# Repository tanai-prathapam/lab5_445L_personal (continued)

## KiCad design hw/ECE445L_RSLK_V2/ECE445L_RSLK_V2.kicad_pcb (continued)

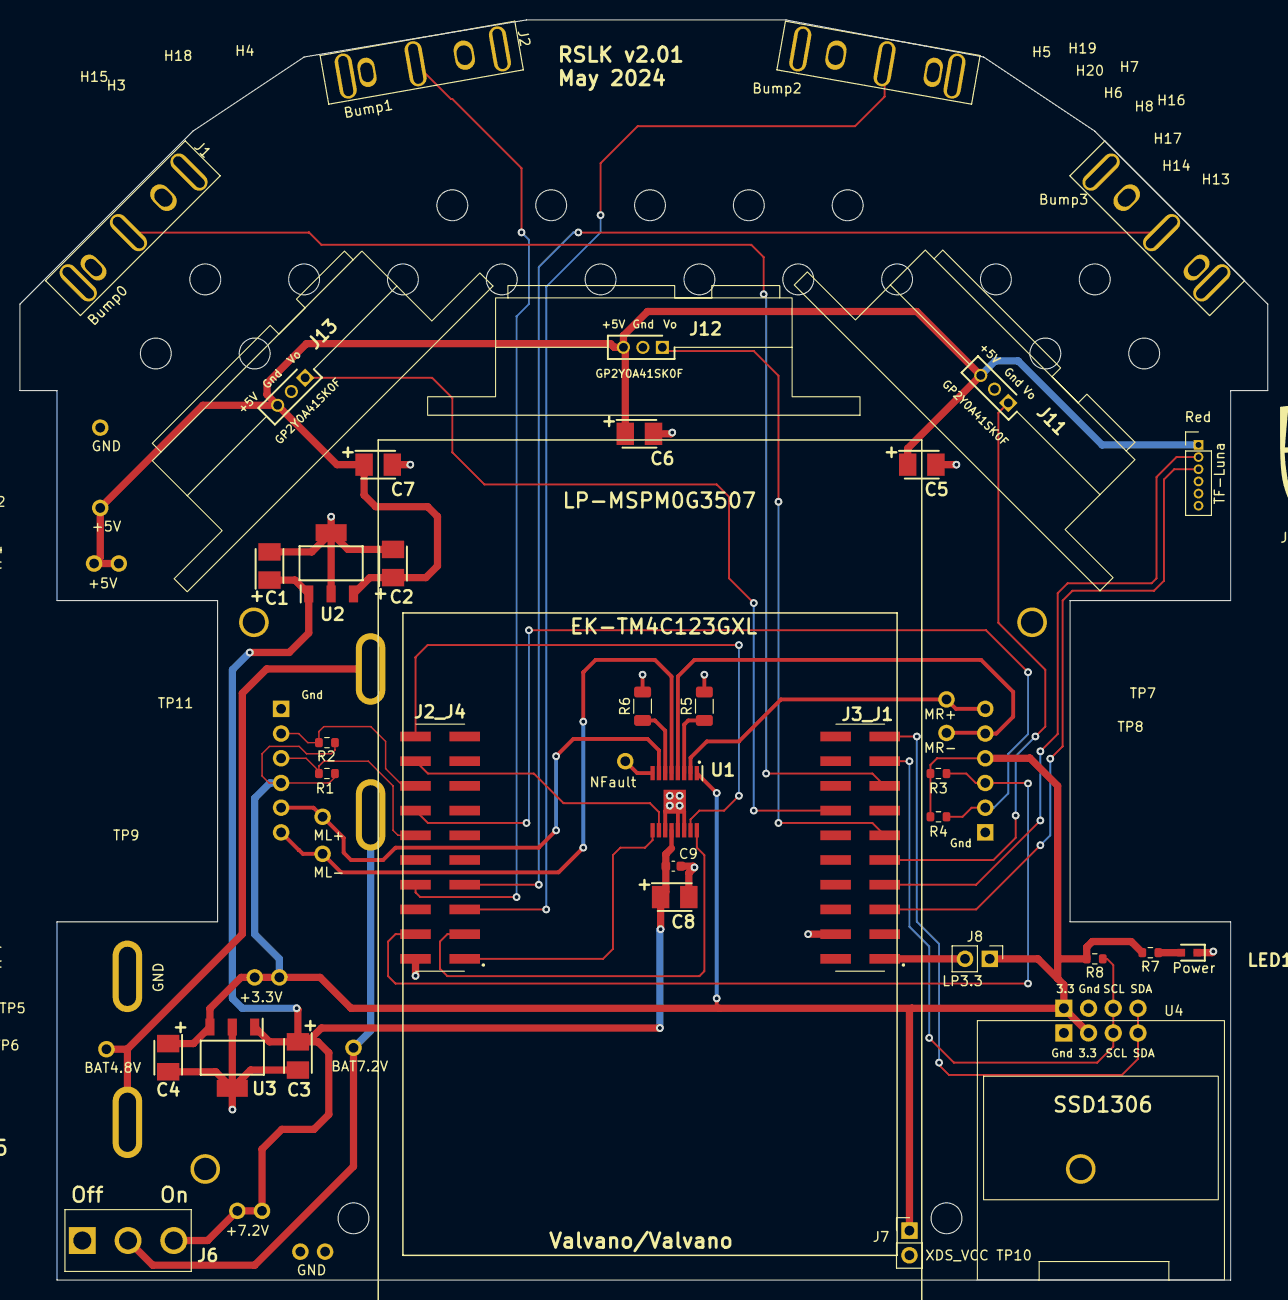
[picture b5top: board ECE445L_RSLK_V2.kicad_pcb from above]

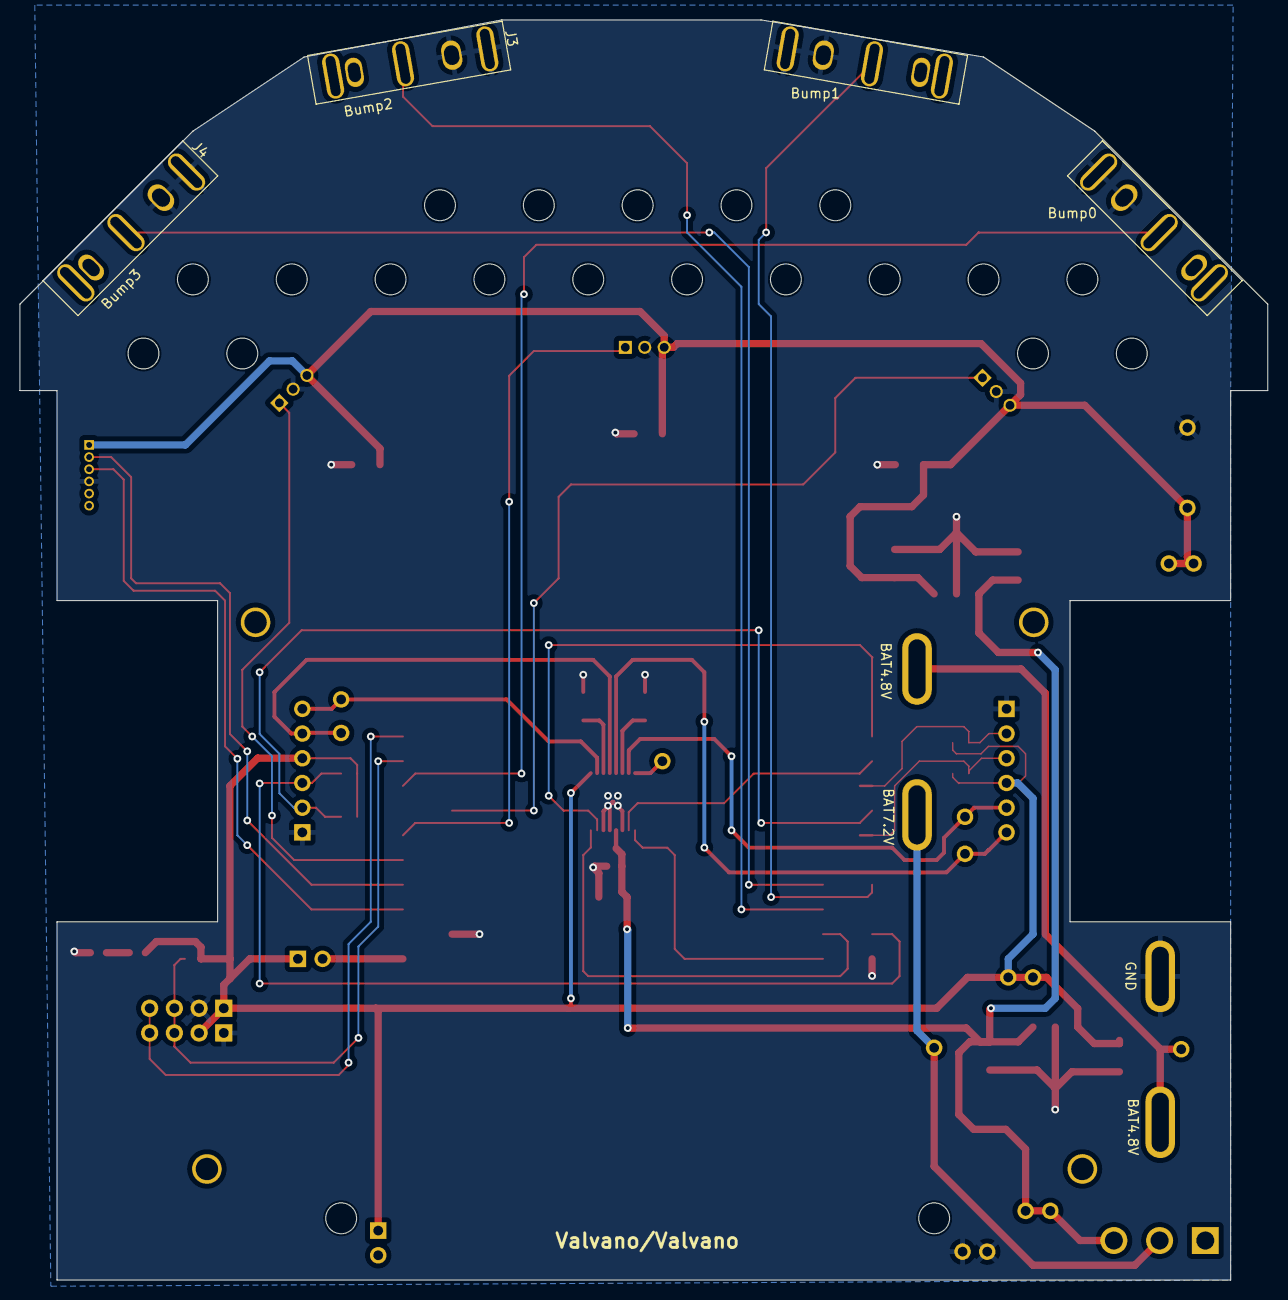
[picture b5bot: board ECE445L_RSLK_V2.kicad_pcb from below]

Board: 2 copper layers, 128.3 x 129.5 mm, 70 parts (2 on the bottom side), 34 nets.

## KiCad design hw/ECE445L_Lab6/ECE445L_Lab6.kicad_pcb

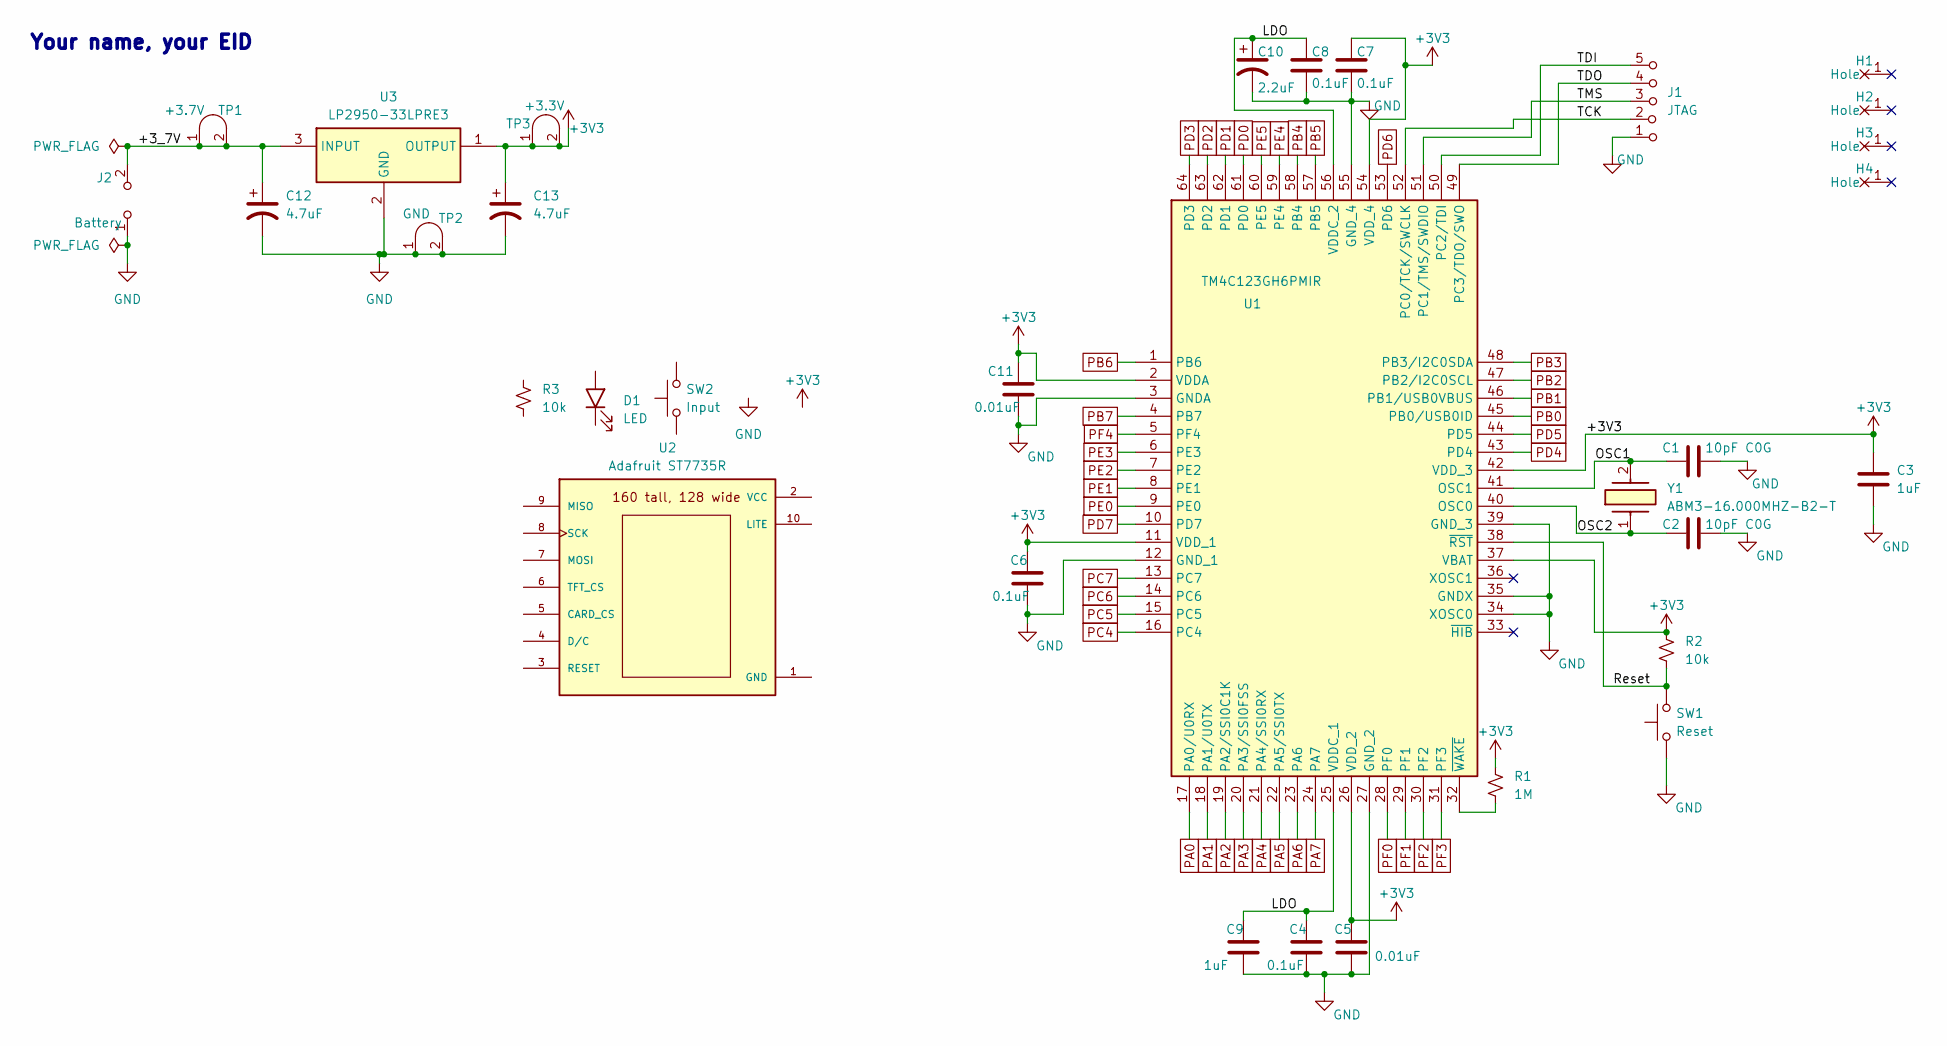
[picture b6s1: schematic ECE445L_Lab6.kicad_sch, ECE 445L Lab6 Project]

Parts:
C1, C2: 10pF C0G; C_Axial_200mil
C3, C9: 1uF; C_Axial_200mil
C4, C6, C7, C8: 0.1uF; C_Axial_200mil
C5, C11: 0.01uF; C_Axial_200mil
C10: 2.2uF; CP_Radial_Tantal200mil
C12, C13: 4.7uF; CP_Radial_Tantal200mil
D1: LED; LED_D5.0mm
H1, H2, H3, H4: MountingHole_4_40
J1: JTAG; PinHeader_1x05_P2.54mm_Vertical
J2: Battery; PinHeader_1x02_P2.54mm_Vertical
R1: 1M; R_Axial_DIN0204_L3.6mm_D1.6mm_P7.62mm_Horizontal
R2, R3: 10k; R_Axial_DIN0204_L3.6mm_D1.6mm_P7.62mm_Horizontal
SW1: Reset; SW_PUSH_6mm
SW2: Input; SW_PUSH_6mm
TP1: +3.7V; Testpoint_1x02_P2.54mm
TP2: GND; Testpoint_1x02_P2.54mm
TP3: +3.3V; Testpoint_1x02_P2.54mm
U1: TM4C123GH6PMIR; QFP50P1200X1200X160-64N; Mouser Part Number 595-TM4C123GH6PMIR
U2: Adafruit ST7735R; adafruit_st7735r2
U3: LP2950-33LPRE3; TO-92_Inline_Wide; Mouser Part Number 595-LP2950-33LPRE3
Y1: ABM3-16.000MHZ-B2-T; ABM3; Mouser Part Number 815-ABM3-16-B2-T

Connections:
+3V3: C3.1, C5.1, C6.1, C7.1, C11.1, C13.1, R1.1, R2.1, TP3.1 (A), TP3.2 (B), U1.2 (VDDA), U1.11 (VDD_1), U1.26 (VDD_2), U1.37 (VBAT), U1.42 (VDD_3), U1.54 (VDD_4), U3.1 (OUTPUT)
/+3_7V: C12.1, J2.2 (B), TP1.1 (A), TP1.2 (B), U3.3 (INPUT)
/LDO: C4.1, C8.1, C9.1, C10.1, U1.25 (VDDC_1), U1.56 (VDDC_2)
/OSC1: C1.1, U1.41 (OSC1), Y1.2
/OSC2: C2.1, U1.40 (OSC0), Y1.1
/Reset: R2.2, SW1.2, U1.38 (~RST)
/TCK: J1.2 (B), U1.52 (PC0/TCK/SWCLK)
/TDI: J1.5 (C), U1.50 (PC2/TDI)
/TDO: J1.4 (C), U1.49 (PC3/TDO/SWO)
/TMS: J1.3 (C), U1.51 (PC1/TMS/SWDIO)
GND: C1.2, C2.2, C3.2, C4.2, C5.2, C6.2, C7.2, C8.2, C9.2, C10.2, C11.2, C12.2, C13.2, J1.1 (A), J2.1 (A), SW1.1, TP2.1 (A), TP2.2 (B), U1.3 (GNDA), U1.12 (GND_1), U1.27 (GND_2), U1.34 (XOSC0), U1.35 (GNDX), U1.39 (GND_3), U1.55 (GND_4), U3.2 (GND)
unnamed: R1.2, U1.32 (~WAKE)
PA0: U1.17 (PA0/U0RX)
PA1: U1.18 (PA1/U0TX)
PA2: U1.19 (PA2/SSI0C1K)
PA3: U1.20 (PA3/SSI0FSS)
PA4: U1.21 (PA4/SSI0RX)
PA5: U1.22 (PA5/SSI0TX)
PA6: U1.23 (PA6)
PA7: U1.24 (PA7)
PB0: U1.45 (PB0/USB0ID)
PB1: U1.46 (PB1/USB0VBUS)
PB2: U1.47 (PB2/I2C0SCL)
PB3: U1.48 (PB3/I2C0SDA)
PB4: U1.58 (PB4)
PB5: U1.57 (PB5)
PB6: U1.1 (PB6)
PB7: U1.4 (PB7)
PC4: U1.16 (PC4)
PC5: U1.15 (PC5)
PC6: U1.14 (PC6)
PC7: U1.13 (PC7)
PD0: U1.61 (PD0)
PD1: U1.62 (PD1)
PD2: U1.63 (PD2)
PD3: U1.64 (PD3)
PD4: U1.43 (PD4)
PD5: U1.44 (PD5)
PD6: U1.53 (PD6)
PD7: U1.10 (PD7)
PE0: U1.9 (PE0)
PE1: U1.8 (PE1)
PE2: U1.7 (PE2)
PE3: U1.6 (PE3)
PE4: U1.59 (PE4)
PE5: U1.60 (PE5)
PF0: U1.28 (PF0)
PF1: U1.29 (PF1)
PF2: U1.30 (PF2)
PF3: U1.31 (PF3)
PF4: U1.5 (PF4)

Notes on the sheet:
Your name, your EID

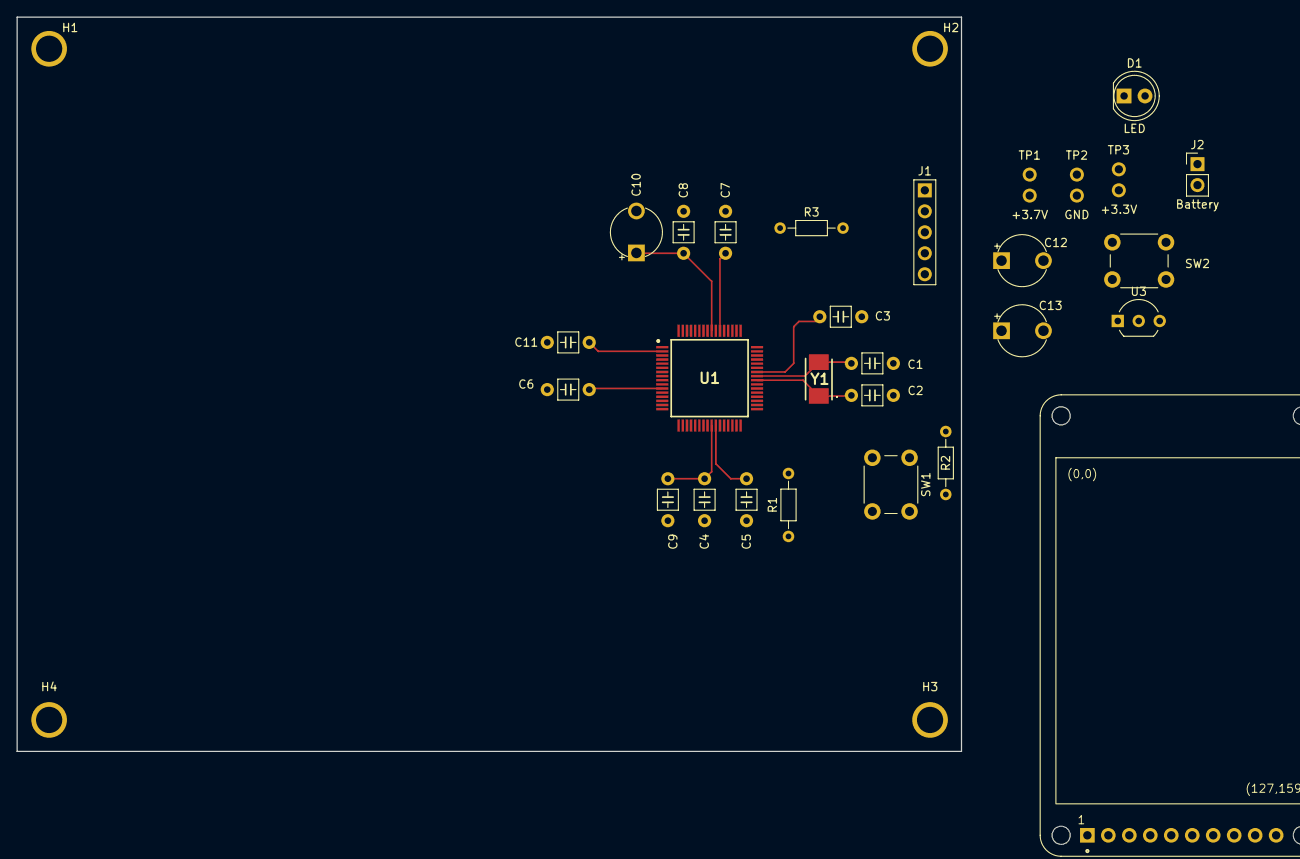
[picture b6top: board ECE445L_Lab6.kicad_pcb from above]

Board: 2 copper layers, 114.4 x 88.9 mm, 32 parts (0 on the bottom side), 12 nets.

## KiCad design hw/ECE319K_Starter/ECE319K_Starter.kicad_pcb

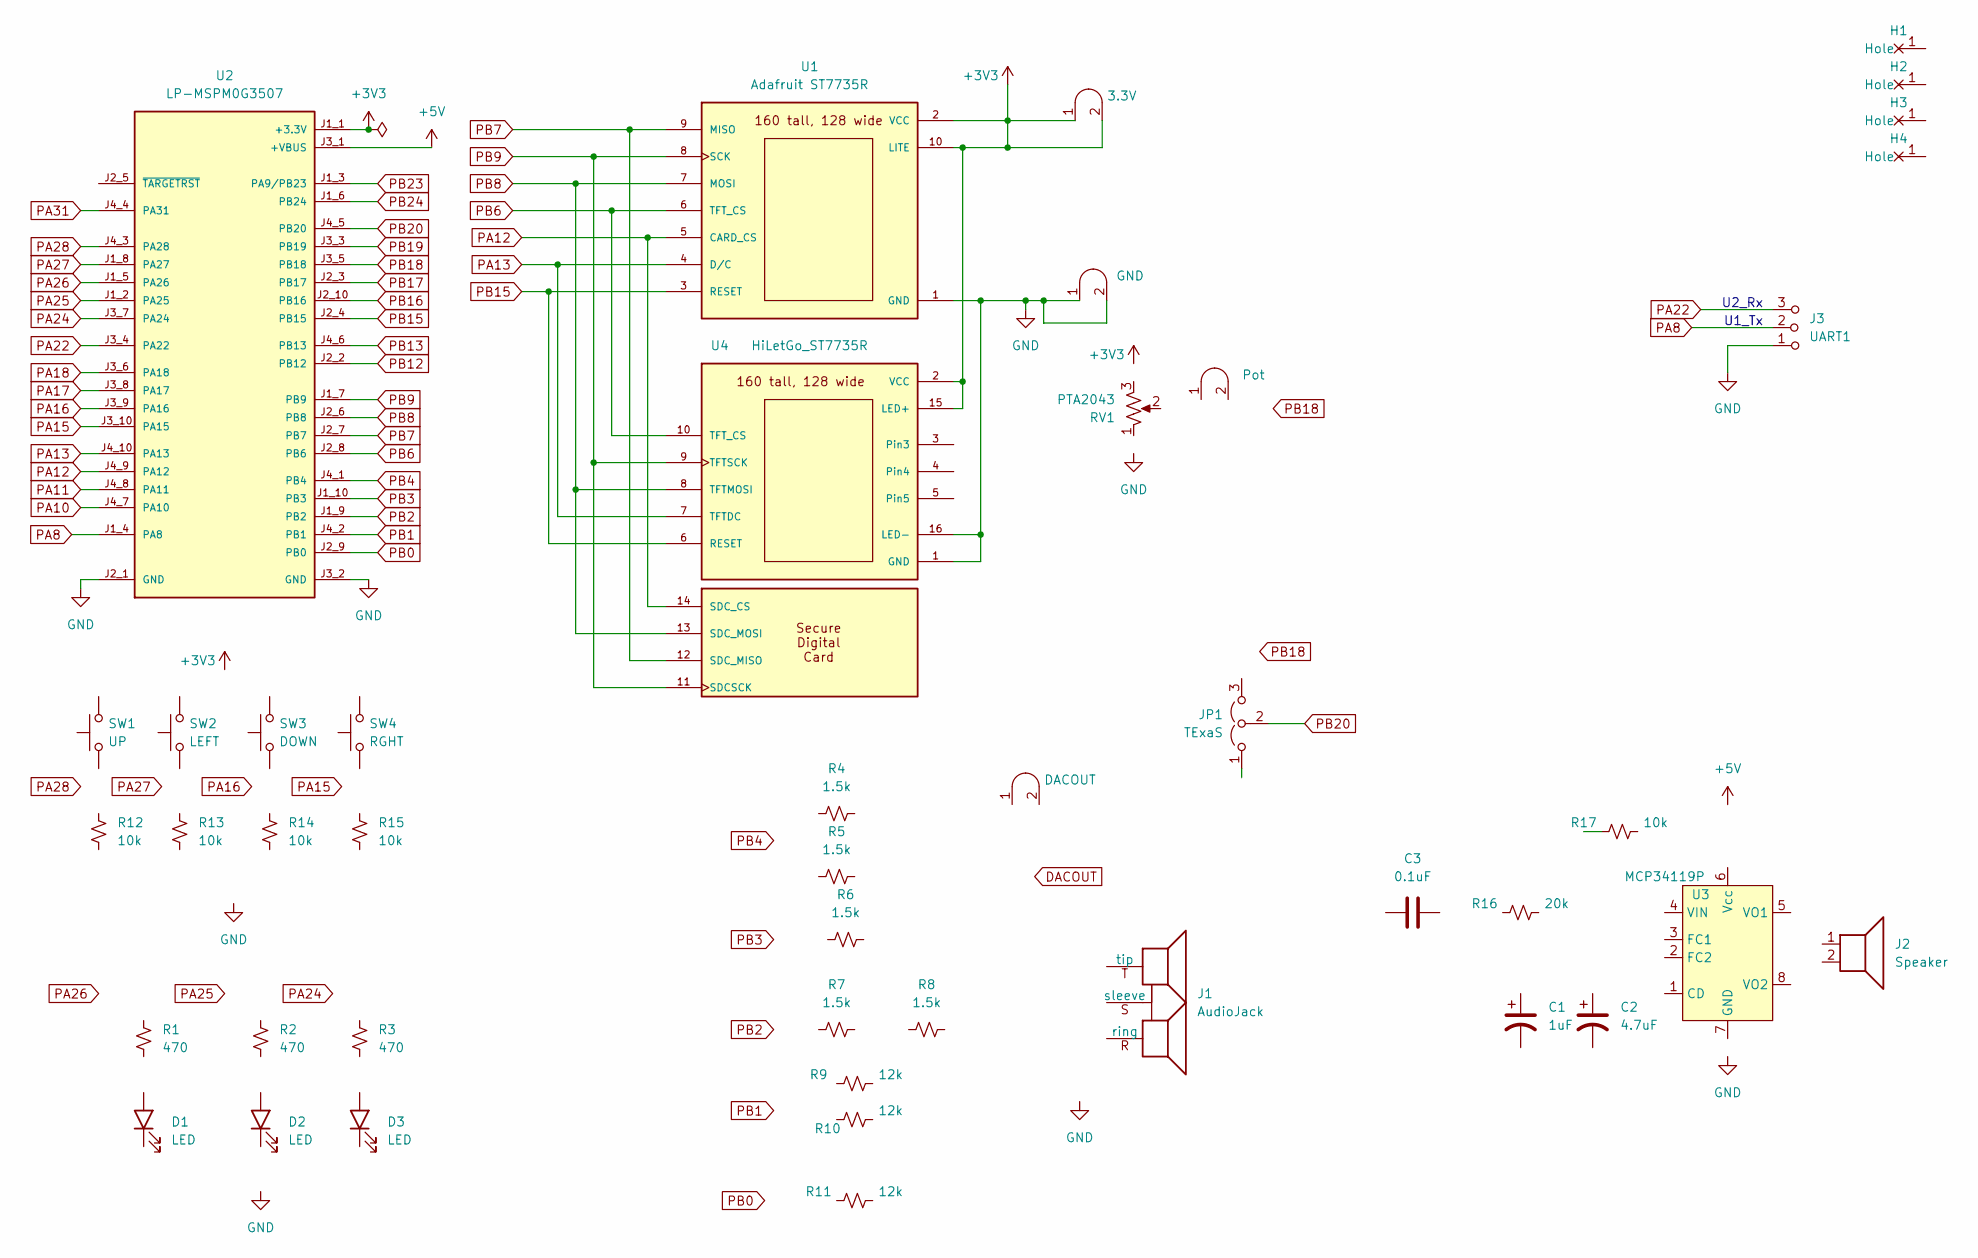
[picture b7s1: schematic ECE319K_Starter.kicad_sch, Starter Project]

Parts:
C1: 1uF; CP_Radial_Tantal200mil
C2: 4.7uF; CP_Radial_Tantal200mil
C3: 0.1uF; C_Axial_200mil
D1, D2, D3: LED; LED_D5.0mm
H1, H2, H3, H4: MountingHole_4_40
J1: AudioJack; Jack_3.5mm_CUI_SJ1-3523N_Horizontal
J2: Speaker; PinHeader_1x02_P2.54mm_Vertical
J3: UART1; PinHeader_1x03_P2.54mm_Vertical
J4: Pot; Testpoint_1x02_P2.54mm
J6: GND; Testpoint_1x02_P2.54mm
J7: DACOUT; Testpoint_1x02_P2.54mm
JP1: TExaS; PinHeader_1x03_P2.54mm_Vertical
R1, R2, R3: 470; R_Axial_DIN0204_L3.6mm_D1.6mm_P7.62mm_Horizontal
R4, R5, R6, R7, R8: 1.5k; R_Axial_DIN0204_L3.6mm_D1.6mm_P7.62mm_Horizontal
R9, R10, R11: 12k; R_Axial_DIN0204_L3.6mm_D1.6mm_P7.62mm_Horizontal
R12, R13, R14, R15, R17: 10k; R_Axial_DIN0204_L3.6mm_D1.6mm_P7.62mm_Horizontal
R16: 20k; R_Axial_DIN0204_L3.6mm_D1.6mm_P7.62mm_Horizontal
RV1: PTA2043; PTA2043pot
SW1: UP; SW_PUSH_6mm
SW2: LEFT; SW_PUSH_6mm
SW3: DOWN; SW_PUSH_6mm
SW4: RGHT; SW_PUSH_6mm
TP1: 3.3V; Testpoint_1x02_P2.54mm
U1: Adafruit ST7735R; adafruit_st7735r2
U2: LP-MSPM0G3507; ti_LP_MSPM0G3507
U3: MCP34119P; DIP-8_W7.62mm_LongPads
U4: HiLetGo_ST7735R; hiletgo_st7735r

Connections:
+3V3: TP1.1 (A), TP1.2 (B), U1.2 (VCC), U1.10 (LITE), U2.J1_1 (+3.3V), U4.2 (VCC), U4.15 (LED+)
+5V: U2.J3_1 (+VBUS)
GND: J3.1 (A), J6.1 (A), J6.2 (B), U1.1 (GND), U2.J2_1 (GND), U2.J3_2 (GND), U4.1 (GND), U4.16 (LED-)
PA8: J3.2 (B), U2.J1_4 (PA8)
PA10: U2.J4_7 (PA10)
PA11: U2.J4_8 (PA11)
PA12: U1.5 (CARD_CS), U2.J4_9 (PA12), U4.14 (SDC_CS)
PA13: U1.4 (D/C), U2.J4_10 (PA13), U4.7 (TFTDC)
PA15: U2.J3_10 (PA15)
PA16: U2.J3_9 (PA16)
PA17: U2.J3_8 (PA17)
PA18: U2.J3_6 (PA18)
PA22: J3.3 (C), U2.J3_4 (PA22)
PA24: U2.J3_7 (PA24)
PA25: U2.J1_2 (PA25)
PA26: U2.J1_5 (PA26)
PA27: U2.J1_8 (PA27)
PA28: U2.J4_3 (PA28)
PA31: U2.J4_4 (PA31)
PB0: U2.J2_9 (PB0)
PB1: U2.J4_2 (PB1)
PB2: U2.J1_9 (PB2)
PB3: U2.J1_10 (PB3)
PB4: U2.J4_1 (PB4)
PB6: U1.6 (TFT_CS), U2.J2_8 (PB6), U4.10 (TFT_CS)
PB7: U1.9 (MISO), U2.J2_7 (PB7), U4.12 (SDC_MISO)
PB8: U1.7 (MOSI), U2.J2_6 (PB8), U4.8 (TFTMOSI), U4.13 (SDC_MOSI)
PB9: U1.8 (SCK), U2.J1_7 (PB9), U4.9 (TFTSCK), U4.11 (SDCSCK)
PB12: U2.J2_2 (PB12)
PB13: U2.J4_6 (PB13)
PB15: U1.3 (RESET), U2.J2_4 (PB15), U4.6 (RESET)
PB16: U2.J2_10 (PB16)
PB17: U2.J2_3 (PB17)
PB18: U2.J3_5 (PB18)
PB19: U2.J3_3 (PB19)
PB20: JP1.2 (C), U2.J4_5 (PB20)
PB23: U2.J1_3 (PA9/PB23)
PB24: U2.J1_6 (PB24)

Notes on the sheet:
U2_Rx
U1_Tx

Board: 2 copper layers, 44 parts (1 on the bottom side), 12 nets, no tracks yet.

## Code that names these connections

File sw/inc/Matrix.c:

// Matrix.c
// Runs on  MSPM0
// Provide functions that initialize GPIO ports and SysTick 
// Use periodic polling
// Jonathan Valvano
// July 18, 2026

/* This example accompanies the book
   "Embedded Systems: Real Time Interfacing to Arm Cortex M Microcontrollers",
   ISBN: 978-1463590154, Jonathan Valvano, copyright (c) 2026

   

Copyright 2026 by Jonathan W. Valvano, valvano@mail.utexas.edu
    You may use, edit, run or distribute this file
    as long as the above copyright notice remains
 THIS SOFTWARE IS PROVIDED "AS IS".  NO WARRANTIES, WHETHER EXPRESS, IMPLIED
 OR STATUTORY, INCLUDING, BUT NOT LIMITED TO, IMPLIED WARRANTIES OF
 MERCHANTABILITY AND FITNESS FOR A PARTICULAR PURPOSE APPLY TO THIS SOFTWARE.
 VALVANO SHALL NOT, IN ANY CIRCUMSTANCES, BE LIABLE FOR SPECIAL, INCIDENTAL,
 OR CONSEQUENTIAL DAMAGES, FOR ANY REASON WHATSOEVER.
 For more information about my classes, my research, and my books, see
 http://users.ece.utexas.edu/~valvano/
 */

// PA27 connected to column 3 (keypad pin 4) using 10K pull-up
// PA26 connected to column 2 (keypad pin 3) using 10K pull-up
// PA25 connected to column 1 (keypad pin 2) using 10K pull-up
// PA24 connected to column 0 (keypad pin 1) using 10K pull-up
// PB3 connected to row 3 (keypad pin 8)
// PB2 connected to row 2 (keypad pin 7)
// PB1 connected to row 1 (keypad pin 6) 
// PB0 connected to row 0 (keypad pin 5)

// [1] [2] [3] [A]
// [4] [5] [6] [B]
// [7] [8] [9] [C]
// [*] [0] [#] [D]
// Pin1 . . . . . . . . Pin8
// Pin 1 -> Column 0 (column starting with 1)
// Pin 2 -> Column 1 (column starting with 2)
// Pin 3 -> Column 2 (column starting with 3)
// Pin 4 -> Column 3 (column starting with A)
// Pin 5 -> Row 0 (row starting with 1)
// Pin 6 -> Row 1 (row starting with 4)
// Pin 7 -> Row 2 (row starting with 7)
// Pin 8 -> Row 3 (row starting with *)

#include <stdint.h>
#include "../inc/FIFO.h"
#include <ti/devices/msp/msp.h>
#include "../inc/LaunchPad.h"
#include "../inc/Clock.h"


uint32_t HeartBeat;  // incremented every 25 ms


void SysTick_IntArm(uint32_t period, uint32_t priority){
  SysTick->CTRL  = 0x00;      // disable during initialization
  SysTick->LOAD  = period-1;  // set reload register
  //The ARM Cortex-M0+ only implements the most significant 2 bits of each 8-bit priority field (giving the 4 priority levels).
  SCB->SHP[1]    = (SCB->SHP[1]&(~0xC0000000))|priority<<30;    // set priority (bits 31,30)
  SysTick->VAL   = 0;         // clear count, cause reload
  SysTick->CTRL  = 0x07;      // Enable SysTick IRQ and SysTick Timer
}


// Initialization of Matrix keypad
void MatrixKeypad_Init(void){ 
// assumes LaunchPad_Init has been called
// PINCM
//   bit 25 is HiZ
//   bit 20 is drive strength (only available for PA10 PA11 PA28 PA31)
//   bit 18 is input enable control
//   bit 17 is pull up control
//   bit 16 is pull down control
//   bit 7 is PC peripheral connected, enable transparent data flow
//   bit 0 selects GPIO function
  IOMUX->SECCFG.PINCM[PB0INDEX] = 0x02000081; // HiZ GPIO output
  IOMUX->SECCFG.PINCM[PB1INDEX] = 0x02000081; // HiZ GPIO output
  IOMUX->SECCFG.PINCM[PB2INDEX] = 0x02000081; // HiZ GPIO output
  IOMUX->SECCFG.PINCM[PB3INDEX] = 0x02000081; // HiZ GPIO output
  GPIOB->DOE31_0 |= 0x0F;     // enable output PB3,2,1,0
  GPIOB->DOUTSET31_0 = 0x0F;  // turn them all off
  IOMUX->SECCFG.PINCM[PA27INDEX] = 0x00060081; // input, pull up
  IOMUX->SECCFG.PINCM[PA26INDEX] = 0x00060081; // input, pull up
  IOMUX->SECCFG.PINCM[PA25INDEX] = 0x00060081; // input, pull up
  IOMUX->SECCFG.PINCM[PA24INDEX] = 0x00060081; // input, pull up
}



struct Row{
  uint32_t PinsToTurnOn;  // output to select row
  uint32_t PinsToTurnOff; // output to deselect row
  char keycode[4];};
typedef const struct Row Row_t;
Row_t ScanTab[5]={
{   0x01, 0x0E, "123A" }, // row 0
{   0x02, 0x0D, "456B" }, // row 1
{   0x04, 0x0B, "789C" }, // row 2
{   0x08, 0x07, "*0#D" }, // row 3
{   0x00, 0x00, "    " }};

/* Returns ASCII code for key pressed,
   Num is the number of keys pressed
   both equal zero if no key pressed */
char MatrixKeypad_Scan(int32_t *Num){
  Row_t *pt;
  char column, key;
  int32_t j;
  (*Num) = 0;
  key = 0;    // default values
  pt = &ScanTab[0];
  while(pt->PinsToTurnOn){
    GPIOB->DOUTSET31_0 = pt->PinsToTurnOff;     // 3 pins are off output
    GPIOB->DOUTCLR31_0 = pt->PinsToTurnOn;      // one pin is on
    Clock_Delay(24);  // adjust this depending on capacitive load
    column = ((GPIOA->DIN31_0&0x0F000000)>>24);// read columns
    for(j=0; j<=3; j++){
      if((column&0x01)==0){
        key = pt->keycode[j];
        (*Num)++;
      }
      column>>=1;  // shift into position
    }
    pt++;
  }
  return key;
}

char static LastKey; 
void Matrix_Init(void){
  LastKey = 0;             // no key typed
  HeartBeat = 0;
  RxFifo_Init();
  MatrixKeypad_Init();     
  SysTick_IntArm(Clock_Freq()/40,2); //40Hz, 25 ms polling
// __enable_irq(); // put enable in main

} 
void SysTick_Handler(void){  char thisKey; int32_t n;
  thisKey = MatrixKeypad_Scan(&n); // scan 
  if((thisKey != LastKey) && (n == 1)){
    RxFifo_Put(thisKey);
    LastKey = thisKey;
  } else if(n == 0){
    LastKey = 0; // invalid
  }
  HeartBeat++;
}
// input ASCII character from keypad
// spin if Fifo is empty
char Matrix_InChar(void){  char letter;
  do{
    letter = RxFifo_Get();
  }
  while(letter == 0);
  return(letter);
}

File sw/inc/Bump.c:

// Bump.c
// RSLK Bumper switches
// negative logic internal pullup
// July 6, 2026
// TM4C MSPM0
// PA5  PA27    Left, Bump 0,
// PF0  PB15    Center Left, Bump 1,
// PB3  PA28    Center Right, Bump 2
// PC4  PA31    Right, Bump 3
#include <ti/devices/msp/msp.h>
#include "../inc/LaunchPad.h"

void Bump_Init(void){
  IOMUX->SECCFG.PINCM[PA27INDEX] = (uint32_t) 0x00060081; // input, pull up
  IOMUX->SECCFG.PINCM[PB15INDEX] = (uint32_t) 0x00060081; // input, pull up
  IOMUX->SECCFG.PINCM[PA28INDEX] = (uint32_t) 0x00060081; // input, pull up
  IOMUX->SECCFG.PINCM[PA31INDEX] = (uint32_t) 0x00060081; // input, pull up
}
// bit 0 is left
// bit 1 is left center
// bit 2 is right center
// bit 3 is right

uint32_t Bump_In(void){
    // PA bit 27 is left
    // PB bit 15 is left center
    // PA bit 28 is right center
    // PA bit 31 is right
  return
    (((GPIOA->DIN31_0&(1<<27))>>(27-0))|  // PA27 into bit 0
     ((GPIOB->DIN31_0&(1<<15))>>(15-1))|  // PB15 into bit 1
     ((GPIOA->DIN31_0&(1<<28))>>(28-2))|  // PA28 into bit 2
     ((GPIOA->DIN31_0&(1<<31))>>(31-3)))  // PA31 into bit 3
     ^0x0F; // convert to positive logic

}

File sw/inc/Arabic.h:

/*!
 * @defgroup Display
 * @brief OLED and LCD displays
 <table>
<caption id="ArabicAdafruitLCDpins">Adafruit ST7735R pins </caption>
<tr><th>Pin <th>Connection <th>Description
<tr><td>10<td>+3.3<td>Backlight
<tr><td>9 <td>nc  <td>SPI1 MISO (used for SDC)
<tr><td>8 <td>PB9 <td>SPI1 SCLK clock out
<tr><td>7 <td>PB8 <td>SPI1 PICO data out
<tr><td>6 <td>PB6 <td>SPI1 CS0=TFT_CS
<tr><td>5 <td>nc  <td>CARD_CS (used for SDC)
<tr><td>4 <td>PA13<td>Data/Command(GPIO), high for data, low for command
<tr><td>3 <td>PB15<td>RESET, low to reset,  (GPIO)
<tr><td>2 <td>+3.3<td>VCC
<tr><td>1 <td>Gnd <td>ground
</table>

 <table>
<caption id="Arabicwidehkpins">wide.hk ST7735R with ADXL345 accelerometer pins </caption>
<tr><th>Pin<th>Connection
<tr><td>VCC  <td> +3.3 V
<tr><td>GND  <td> Ground
<tr><td>!SCL <td> SPI1 SCLK: PB9 clock
<tr><td>!SDA <td> SPI1 PICO: PB8 MOSI SPI data from microcontroller to TFT or SDC
<tr><td>DC   <td> GPIO       PA13 TFT data/command
<tr><td>RES  <td> GPIO       PB15 TFT reset
<tr><td>CS   <td> SPI1 CS0:  PB6 TFT_CS, active low to enable TFT
<tr><td>*CS  <td> (NC) SDC_CS, active low to enable SDC
<tr><td>MISO <td> (NC) MISO SPI data from SDC to microcontroller
<tr><td>SDA  <td> (NC) I2C data for ADXL345 accelerometer
<tr><td>SCL  <td> (NC) I2C clock for ADXL345 accelerometer
<tr><td>SDO  <td> (NC) I2C alternate address for ADXL345 accelerometer
<tr><td>Backlight + - Light, backlight connected to +3.3 V
</table>


<table>
<caption id="Arabicwidehkpins335">wide.hk ST7735R with ADXL335 accelerometer pins </caption>
<tr><th>Pin<th>Connection
<tr><td>VCC  <td> +3.3 V
<tr><td>GND  <td> Ground
/<tr><td>!SCL<td> SPI1 SCLK: PB9
<tr><td>!SDA <td> SPI1 PICO: PB8 MOSI SPI data from microcontroller to TFT or SDC
<tr><td>DC   <td> GPIO       PA13 TFT data/command
<tr><td>RES  <td> GPIO       PB15 TFT reset
<tr><td>CS   <td> SPI1 CS0:  PB6 TFT_CS, active low to enable TFT
<tr><td>*CS  <td> (NC) SDC_CS, active low to enable SDC
<tr><td>MISO <td> (NC) MISO SPI data from SDC to microcontroller
<tr><td>X<td> (NC) analog input X-axis from ADXL335 accelerometer
<tr><td>Y<td> (NC) analog input Y-axis from ADXL335 accelerometer
<tr><td>Z<td> (NC) analog input Z-axis from ADXL335 accelerometer
<tr><td>Backlight + <td> Light, backlight connected to +3.3 V
</table>

<table>
<caption id="ArabicHiLetgopins">HiLetgo ST7735 TFT and SDC pins </caption>
<tr><th>signal<th>Pin<th>Connection
<tr><td>LED-   <td>16<td>TFT, to ground
<tr><td>LED+   <td>15<td>TFT, to +3.3 V
<tr><td>SD_CS  <td>14<td>SDC, to chip select
<tr><td>MOSI   <td>13<td>SDC, to MOSI
<tr><td>MISO   <td>12<td>SDC, to MISO
<tr><td>SCK    <td>11<td>SDC, to serial clock
<tr><td>CS     <td>10<td>TFT, to PB6  SPI1 CS0
<tr><td>SCL    <td> 9<td>TFT, to PB9  SPI1 SCLK
<tr><td>SDA    <td> 8<td>TFT, to PB8  MOSI SPI1 PICO
<tr><td>A0     <td> 7<td>TFT, to PA13 Data/Command, high for data, low for command
<tr><td>RESET  <td> 6<td>TFT, to PB15 reset (GPIO), low to reset
<tr><td>NC     <td>3,4,5<td>not connected
<tr><td>VCC    <td> 2<td>to +3.3 V
<tr><td>GND    <td> 1<td>to ground
</table>

<table>
<caption id="ArabicTyenazapins">Tyenaza Tyenazaqhf72mi9s3 pins </caption>
<tr><th>signal<th>Pin<th>Connection
<tr><td>LED <td>8<td> to +3.3 V
<tr><td>SCK <td>7<td>SCLK         to PB9 SPI1 SCLK
<tr><td>SDA <td>6<td>MOSI,        to PB8 SPI1 PICO
<tr><td>A0  <td>5<td>Data/Command to PA13 (GPIO), high for data, low for command
<tr><td>RESET <td>4<td>to PB15 (GPIO), low to reset
<tr><td>CS  <td>3<td>to PB6 SPI1 CS0:
<tr><td>Gnd <td>2<td>to ground
<tr><td>VCC <td>1<td>to +3.3 V
</table>
 * @{*/
/**
 * @file      Arabic.h
 * @brief     Arabic output to LCD
 * @details   Arabic character/string output to ST7735R display<br>
 * @version   ECE319K v1.0
 * @author    Amina Meddad and Jonathan Valvano
 * @copyright Copyright 2024 by Jonathan W. Valvano, valvano@mail.utexas.edu,
 * @warning   AS-IS
 * @note      For more information see  http://users.ece.utexas.edu/~valvano/
 * @date      August 14, 2024
  <table>
<caption id="ArabicAdafruitLCDpins2">Adafruit ST7735R pins </caption>
<tr><th>Pin <th>Connection <th>Description
<tr><td>10<td>+3.3<td>Backlight
<tr><td>9 <td>nc  <td>SPI1 MISO (used for SDC)
<tr><td>8 <td>PB9 <td>SPI1 SCLK clock out
<tr><td>7 <td>PB8 <td>SPI1 PICO data out
<tr><td>6 <td>PB6 <td>SPI1 CS0=TFT_CS
<tr><td>5 <td>nc  <td>CARD_CS (used for SDC)
<tr><td>4 <td>PA13<td>Data/Command(GPIO), high for data, low for command
<tr><td>3 <td>PB15<td>RESET, low to reset,  (GPIO)
<tr><td>2 <td>+3.3<td>VCC
<tr><td>1 <td>Gnd <td>ground
</table>

 <table>
<caption id="Arabicwidehkpins2">wide.hk ST7735R with ADXL345 accelerometer pins </caption>
<tr><th>Pin<th>Connection
<tr><td>VCC  <td> +3.3 V
<tr><td>GND  <td> Ground
<tr><td>!SCL <td> SPI1 SCLK: PB9 clock
<tr><td>!SDA <td> SPI1 PICO: PB8 MOSI SPI data from microcontroller to TFT or SDC
<tr><td>DC   <td> GPIO       PA13 TFT data/command
<tr><td>RES  <td> GPIO       PB15 TFT reset
<tr><td>CS   <td> SPI1 CS0:  PB6 TFT_CS, active low to enable TFT
<tr><td>*CS  <td> (NC) SDC_CS, active low to enable SDC
<tr><td>MISO <td> (NC) MISO SPI data from SDC to microcontroller
<tr><td>SDA  <td> (NC) I2C data for ADXL345 accelerometer
<tr><td>SCL  <td> (NC) I2C clock for ADXL345 accelerometer
<tr><td>SDO  <td> (NC) I2C alternate address for ADXL345 accelerometer
<tr><td>Backlight + - Light, backlight connected to +3.3 V
</table>


<table>
<caption id="Arabicwidehkpins3352">wide.hk ST7735R with ADXL335 accelerometer pins </caption>
<tr><th>Pin<th>Connection
<tr><td>VCC  <td> +3.3 V
<tr><td>GND  <td> Ground
/<tr><td>!SCL<td> SPI1 SCLK: PB9
<tr><td>!SDA <td> SPI1 PICO: PB8 MOSI SPI data from microcontroller to TFT or SDC
<tr><td>DC   <td> GPIO       PA13 TFT data/command
<tr><td>RES  <td> GPIO       PB15 TFT reset
<tr><td>CS   <td> SPI1 CS0:  PB6 TFT_CS, active low to enable TFT
<tr><td>*CS  <td> (NC) SDC_CS, active low to enable SDC
<tr><td>MISO <td> (NC) MISO SPI data from SDC to microcontroller
<tr><td>X<td> (NC) analog input X-axis from ADXL335 accelerometer
<tr><td>Y<td> (NC) analog input Y-axis from ADXL335 accelerometer
<tr><td>Z<td> (NC) analog input Z-axis from ADXL335 accelerometer
<tr><td>Backlight + <td> Light, backlight connected to +3.3 V
</table>

<table>
<caption id="ArabicHiLetgopins2">HiLetgo ST7735 TFT and SDC pins </caption>
<tr><th>signal<th>Pin<th>Connection
<tr><td>LED-   <td>16<td>TFT, to ground
<tr><td>LED+   <td>15<td>TFT, to +3.3 V
<tr><td>SD_CS  <td>14<td>SDC, to chip select
<tr><td>MOSI   <td>13<td>SDC, to MOSI
<tr><td>MISO   <td>12<td>SDC, to MISO
<tr><td>SCK    <td>11<td>SDC, to serial clock
<tr><td>CS     <td>10<td>TFT, to PB6  SPI1 CS0
<tr><td>SCL    <td> 9<td>TFT, to PB9  SPI1 SCLK
<tr><td>SDA    <td> 8<td>TFT, to PB8  MOSI SPI1 PICO
<tr><td>A0     <td> 7<td>TFT, to PA13 Data/Command, high for data, low for command
<tr><td>RESET  <td> 6<td>TFT, to PB15 reset (GPIO), low to reset
<tr><td>NC     <td>3,4,5<td>not connected
<tr><td>VCC    <td> 2<td>to +3.3 V
<tr><td>GND    <td> 1<td>to ground
</table>

<table>
<caption id="ArabicTyenazapins2">Tyenaza Tyenazaqhf72mi9s3 pins </caption>
<tr><th>signal<th>Pin<th>Connection
<tr><td>LED <td>8<td> to +3.3 V
<tr><td>SCK <td>7<td>SCLK         to PB9 SPI1 SCLK
<tr><td>SDA <td>6<td>MOSI,        to PB8 SPI1 PICO
<tr><td>A0  <td>5<td>Data/Command to PA13 (GPIO), high for data, low for command
<tr><td>RESET <td>4<td>to PB15 (GPIO), low to reset
<tr><td>CS  <td>3<td>to PB6 SPI1 CS0:
<tr><td>Gnd <td>2<td>to ground
<tr><td>VCC <td>1<td>to +3.3 V
</table>
<br>

  ******************************************************************************/

#ifndef _ARABIC_
#define _ARABIC_
#include <stdint.h>
/**
 * \brief Arabic character set
 */
typedef enum {null,alif,ayh,baa,daad,daal,dhaa,dhaal,faa,ghayh,haa,ha,jeem,kaaf,khaa,laam,meem,noon,qaaf,raa,saad,seen,sheen,ta,thaa,twe,waaw,yaa,zaa,space,dot} Arabic_t;

/**
 * Move the cursor to the desired X- and Y-position.  The
 * next character will be printed here.  X=0 is the leftmost
 * column.  Y=0 is the top row. *
 * @param none
 * @param newX  new X-position of the cursor (0<=newX<=7)
 * @param newY  new Y-position of the cursor (0<=newY<=9)
 * @return none
 * @brief  Move Arabic cursor
 */
void Arabic_SetCursor(uint32_t newX, uint32_t newY);

/**
 * Output one Arabic character to the LCD
 * Position determined by Arabic_SetCursor command
 * Color set by ST7735_SetTextColor
 * @param ch 8-bit Arabic character
 * @return none
 * @brief  Output an Arabic character
 */
void Arabic_OutChar(Arabic_t ch);

/**
 * Output an Arabic string to the LCD
 * Position determined by Arabic_SetCursor command
 * Color set by ST7735_SetTextColor.
 * The string will automatically wrap.
 * @param ptr  pointer to null-terminated Arabic string
 * @return none
 * @brief  Output an Arabic string
 */
void Arabic_OutString(Arabic_t *ptr);
#endif
/** @}*/

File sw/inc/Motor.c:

/* Motor.c
 * Jonathan Valvano
 * v2.0.3
 * July 13, 2026
// Motor
//   MSPM0
//    PB4  Motor_PWML, ML+, IN3, PWM TIMA1_C0
//    PB1  Motor_PWMR, MR+, IN1, PWM TIMA1_C1
//    PB0  Motor_DIR_L,ML-, IN4, GPIO 0 means forward, 1 means backward
//    PB16 Motor_DIR_R,MR-, IN2, GPIO 0 means forward, 1 means backward

 */
#include <ti/devices/msp/msp.h>
#include "../inc/LaunchPad.h"
#include "../inc/Clock.h"
#include "../inc/PWM1.h"
#include "../inc/Motor.h"
#define DIR_L 1
#define DIR_R (1<<16)

void Motor_Init(void){
  // ****ECE445L write this ****


}

void Motor_Forward(uint32_t dutyLeft, uint32_t dutyRight){
  // ****ECE445L write this ****

  
}

void Motor_Backward(uint32_t dutyLeft, uint32_t dutyRight){
    // ****ECE445L write this ****

 
}
void Motor_Right(uint32_t dutyLeft, uint32_t dutyRight){
    // ****ECE445L write this ****

}
void Motor_Left(uint32_t dutyLeft, uint32_t dutyRight){
   // ****ECE445L write this ****


}
